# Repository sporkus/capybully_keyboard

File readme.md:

Capybully
---

Open source capactive sensing pcb for [Bully keyboard](https://mkh.works/#bully).

### Status
PCB has been tested and is fully functional with Niz and Deskeys parts.

### Specs
- MCU: stm32F072CB

### Supported layouts

### Production files
JLCPCB [production files](pcb_production) are provided. Component positions have been verified, but as always, do your own diligence when ordering.

#### Firmware
- [See here](./firmware) for instructions, links to qmk/vial config and binaries.

#### Hardware
- 25x m2 brass standoff. 5mm long x 3mm diameter
- 50x m2 low profile screws

## Misc
#### 3D assembly preview
* [online viewer](https://3dviewer.net/#model=https://github.com/sporkus/capybully_keyboard/blob/dev/documentation/capybully-3D.step)
* [step assembly](./documentation/capybully-3D.step)

#### PCB Renders

#### Interactive BoM
Download and open this [html](./documentation/capybully-ibom.html) locally

#### Schematic
[pdf](./documentation/capybully-schematic.pdf)

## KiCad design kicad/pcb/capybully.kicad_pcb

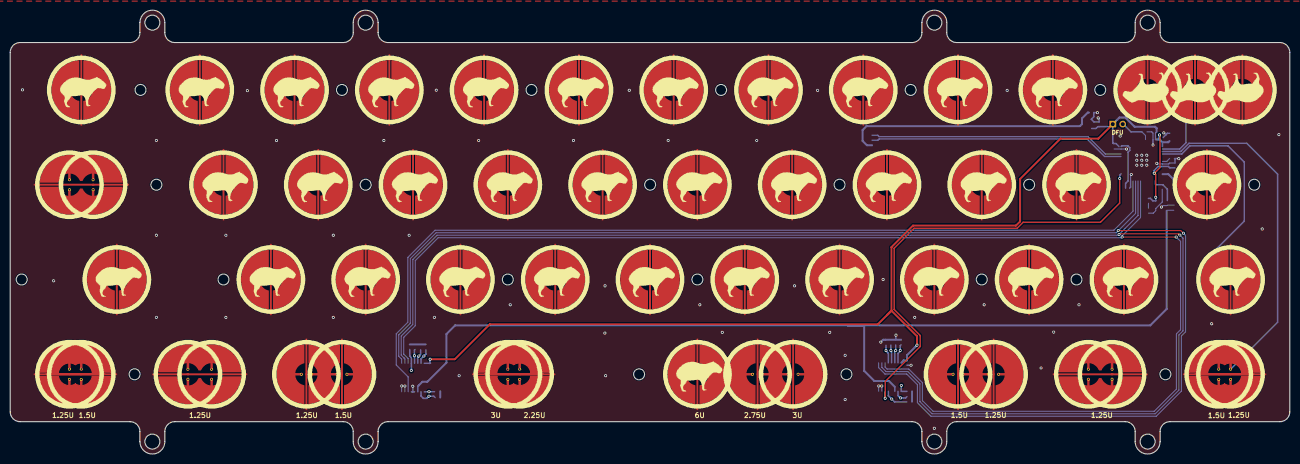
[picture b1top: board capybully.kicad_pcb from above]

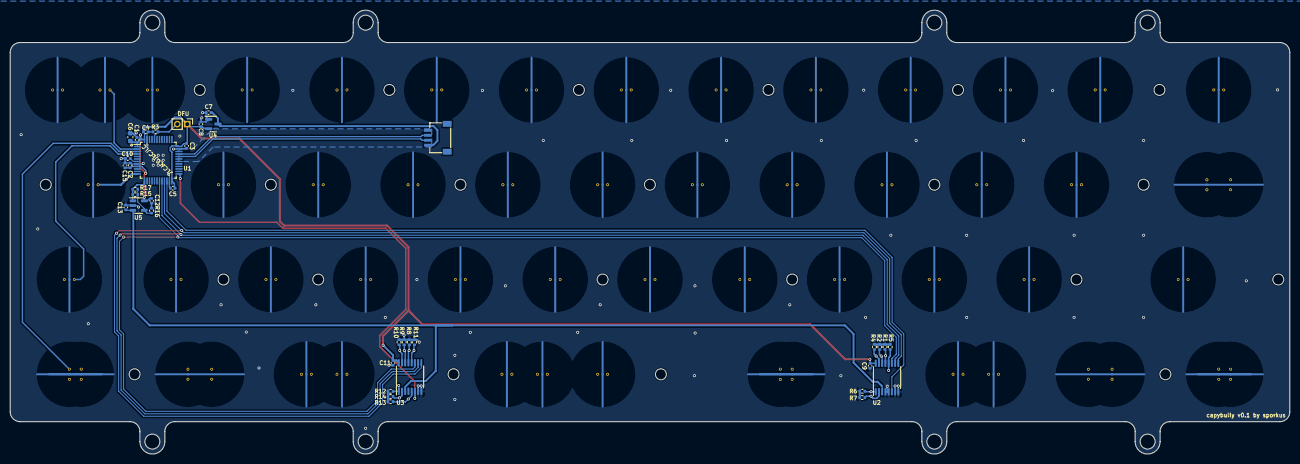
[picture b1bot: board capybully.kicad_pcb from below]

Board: 4 copper layers, 257.2 x 89.2 mm, 107 parts (38 on the bottom side), 32 nets.

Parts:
C1, C2, C3, C4, C10: 100nF; C_0402_1005Metric
C5, C9, C11, C12: 100n; C_0402_1005Metric
C6: 10uF; C_0603_1608Metric
C7, C8: 1uF; C_0402_1005Metric
C13: 220pF NP0; C_0402_1005Metric
C15: 1u; C_0402_1005Metric
H1, H2, H3, H4, H5, H6, H7, H8, H9, H10, H11, H12, H13, H14, H15, H16, H17, H18, H19, H20, H21, H22: MountingHole; MountingHole_2.2mm_M2_DIN965
J1: SM04B-SRSS-TB(LF)(SN); JST-SR-4
R1, R2, R4, R5, R6, R7, R8, R9, R10, R11, R12, R13, R14, R15: 100k; R_0402_1005Metric
R3: 10k; R_0402_1005Metric
R16: 1k; R_0402_1005Metric
R17: DNP; R_0402_1005Metric
SW1, SW2, SW3, SW4, SW5, SW6, SW7, SW8, SW9, SW10, SW11, SW12, SW13, SW14, SW16, SW17, SW18, SW19, SW20, SW21, SW22, SW23, SW24, SW25, SW26, SW27, SW28, SW29, SW30, SW31, SW32, SW33, SW34, SW35, SW36, SW37, SW38, SW43: EC_SW; capy_pad_1U
SW15: EC_SW; ecs_pad_1.75u_1.25u_combo
SW39, SW42, SW47: EC_SW; ecs_pad_combo_0.125u_offset
SW40, SW46: EC_SW; ecs_pad_combo_0.25u_offset
SW41, SW44, SW45: EC_SW; ecs_pad_combo_0.375u_offset
SW100: DFU; PinHeader_1x02_P2.00mm_Vertical
U1: STM32F072CBT6; LQFP-48_7x7mm_P0.5mm
U2, U3: 74HC4051; TSSOP-16_4.4x5mm_P0.65mm
U4: XC6206PxxxMR-Regulator_Linear; SOT-23
U5: OPA354; SOT-23-5

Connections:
+3V3: C1.1, C2.1, C3.1, C4.1, C5.1, C6.1, C8.2, C9.2, C11.2, C12.2, C15.1, SW100.1, U1.1 (VBAT), U1.9 (VDDA), U1.24 (VDD), U1.36 (VDDIO2), U1.48 (VDD), U2.16 (VCC), U3.16 (VCC), U4.2 (VO), U5.5 (V+)
+5V: C7.2, J1.1, U4.3 (VI)
ADC: R15.1, R17.1, U1.13 (PA3), U5.1
APLEX_0_A0: R1.1, SW2.2, SW16.2, SW28.2, SW40.1, U2.13 (A0)
APLEX_0_A1: R2.1, SW3.2, SW17.2, SW29.2, SW41.2, U2.14 (A1)
APLEX_0_A2: R4.1, SW4.2, SW18.2, SW30.2, U2.15 (A2)
APLEX_0_A3: R5.1, SW1.2, SW15.1, SW27.1, SW39.2, U2.12 (A3)
APLEX_0_A4: R6.1, SW5.2, SW19.2, SW31.2, SW42.1, U2.1 (A4)
APLEX_0_A6: R7.1, SW6.2, SW20.2, SW32.2, SW43.1, U2.2 (A6)
APLEX_0_EN: U1.22 (PB11), U2.6 (~E)
APLEX_1_A0: R8.1, SW8.2, SW22.2, SW34.2, U3.13 (A0)
APLEX_1_A1: R9.1, SW9.2, SW23.2, SW35.2, U3.14 (A1)
APLEX_1_A2: R10.1, SW10.2, SW24.2, SW36.2, SW45.2, U3.15 (A2)
APLEX_1_A3: R11.1, SW7.2, SW21.2, SW33.2, SW44.2, U3.12 (A3)
APLEX_1_A4: R12.1, SW11.2, SW25.2, SW37.2, SW46.2, U3.1 (A4)
APLEX_1_A5: R13.1, SW13.1, SW14.2, U3.5 (A5)
APLEX_1_A6: R14.1, SW12.2, SW26.2, SW38.2, SW47.1, U3.2 (A6)
APLEX_1_EN: U1.25 (PB12), U3.6 (~E)
APLEX_OUT: C13.1, U2.3 (A), U3.3 (A), U5.3 (+)
APLEX_SEL0: U1.19 (PB1), U2.11 (S0), U3.11 (S0)
APLEX_SEL1: U1.20 (PB2), U2.10 (S1), U3.10 (S1)
APLEX_SEL2: U1.21 (PB10), U2.9 (S2), U3.9 (S2)
BOOT0: R3.1, SW100.2, U1.44 (BOOT0)
D_N: J1.2, U1.32 (PA11)
D_P: J1.3, U1.33 (PA12)
GND: C1.2, C2.2, C3.2, C4.2, C5.2, C6.2, C7.1, C8.1, C9.1, C10.2, C11.1, C12.1, C13.2, C15.2, J1.4, R1.2, R2.2, R3.2, R4.2, R5.2, R6.2, R7.2, R8.2, R9.2, R10.2, R11.2, R12.2, R13.2, R14.2, R16.2, SW1.3 (SG), SW2.3 (SG), SW3.3 (SG), SW4.3 (SG), SW5.3 (SG), SW6.3 (SG), SW7.3 (SG), SW8.3 (SG), SW9.3 (SG), SW10.3 (SG), SW11.3 (SG), SW12.3 (SG), SW13.3 (SG), SW14.3 (SG), SW15.3 (SG), SW16.3 (SG), SW17.3 (SG), SW18.3 (SG), SW19.3 (SG), SW20.3 (SG), SW21.3 (SG), SW22.3 (SG), SW23.3 (SG), SW24.3 (SG), SW25.3 (SG), SW26.3 (SG), SW27.3 (SG), SW28.3 (SG), SW29.3 (SG), SW30.3 (SG), SW31.3 (SG), SW32.3 (SG), SW33.3 (SG), SW34.3 (SG), SW35.3 (SG), SW36.3 (SG), SW37.3 (SG), SW38.3 (SG), SW39.3 (SG), SW40.3 (SG), SW41.3 (SG), SW42.3 (SG), SW43.3 (SG), SW44.3 (SG), SW45.3 (SG), SW46.3 (SG), SW47.3 (SG), U1.8 (VSSA), U1.23 (VSS), U1.35 (VSS), U1.47 (VSS), U2.4 (A7), U2.5 (A5), U2.7 (VEE), U2.8 (GND), U3.4 (A7), U3.7 (VEE), U3.8 (GND), U4.1 (GND), U5.2 (V-)
NRST: C10.1, U1.7 (NRST)
unnamed: R15.2, R16.1, R17.2, U5.4 (-)
ROW0: SW1.1, SW2.1, SW3.1, SW4.1, SW5.1, SW6.1, SW7.1, SW8.1, SW9.1, SW10.1, SW11.1, SW12.1, SW13.2, SW14.1, U1.2 (PC13)
ROW1: SW15.2, SW16.1, SW17.1, SW18.1, SW19.1, SW20.1, SW21.1, SW22.1, SW23.1, SW24.1, SW25.1, SW26.1, U1.12 (PA2)
ROW2: SW27.2, SW28.1, SW29.1, SW30.1, SW31.1, SW32.1, SW33.1, SW34.1, SW35.1, SW36.1, SW37.1, SW38.1, U1.4 (PC15)
ROW3: SW39.1, SW40.2, SW41.1, SW42.2, SW43.2, SW44.1, SW45.1, SW46.1, SW47.2, U1.3 (PC14)

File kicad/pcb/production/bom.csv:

Designator,Footprint,Quantity,Value,LCSC Part #
"C1, C10, C2, C3, C4",0402,5,100nF,C307331
"C11, C12, C5, C9",0402,4,100n,C307331
C13,0402,1,220pF NP0,C1530
C15,0402,1,1u,
C6,0603,1,10uF,
"C7, C8",0402,2,1uF,C52923
"H1, H10, H11, H12, H13, H14, H15, H16, H17, H18, H19, H2, H20, H21, H22, H23, H24, H25, H26, H27, H3, H4, H5, H6, H7, H8, H9",MountingHole_2.2mm_M2_DIN965,27,MountingHole,
J1,JST-SR-4,1,SM04B-SRSS-TB(LF)(SN),
"R1, R10, R11, R12, R13, R14, R15, R2, R4, R5, R6, R7, R8, R9",0402,14,100k,C25741
R16,0402,1,1k,C11702
R3,0402,1,10k,
U1,LQFP-48_7x7mm_P0.5mm,1,STM32F072CBT6,
"U2, U3",TSSOP-16_4.4x5mm_P0.65mm,2,74HC4051,C5645
U4,SOT-23,1,XC6206PxxxMR-Regulator_Linear,C5446
U5,SOT-23-5,1,OPA354,

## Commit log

2023-07-20 init
2023-07-20 docs
2023-07-20 [kibot]
2023-07-20 doc fix
2023-07-25 should be ok for proto order
2023-08-09 add license
2023-08-09 adding right shift option
2023-08-17 updated plate files
2023-08-17 change plate thickness to 1.2mm
2023-08-17 plate files workflow
2023-08-17 adding edgecut to mounting hole
2023-08-18 fixed plate silkscreen
2023-08-18 fix 3u sch for kibot
2023-08-23 trying universal plate
2023-08-23 change topre plate to non-stepped cap
2023-08-23 fix workflow path
2023-08-31 add precompiled firmware and instructions
2023-09-10 updated footprint and fixing plate tolerance
2023-09-10 add qr
2023-09-11 update lib
2023-09-11 update 3d model
2023-09-11 step preview link
2023-09-11 updated layout img
2023-09-21 removing layout options for plates
2023-10-19 v1 release
